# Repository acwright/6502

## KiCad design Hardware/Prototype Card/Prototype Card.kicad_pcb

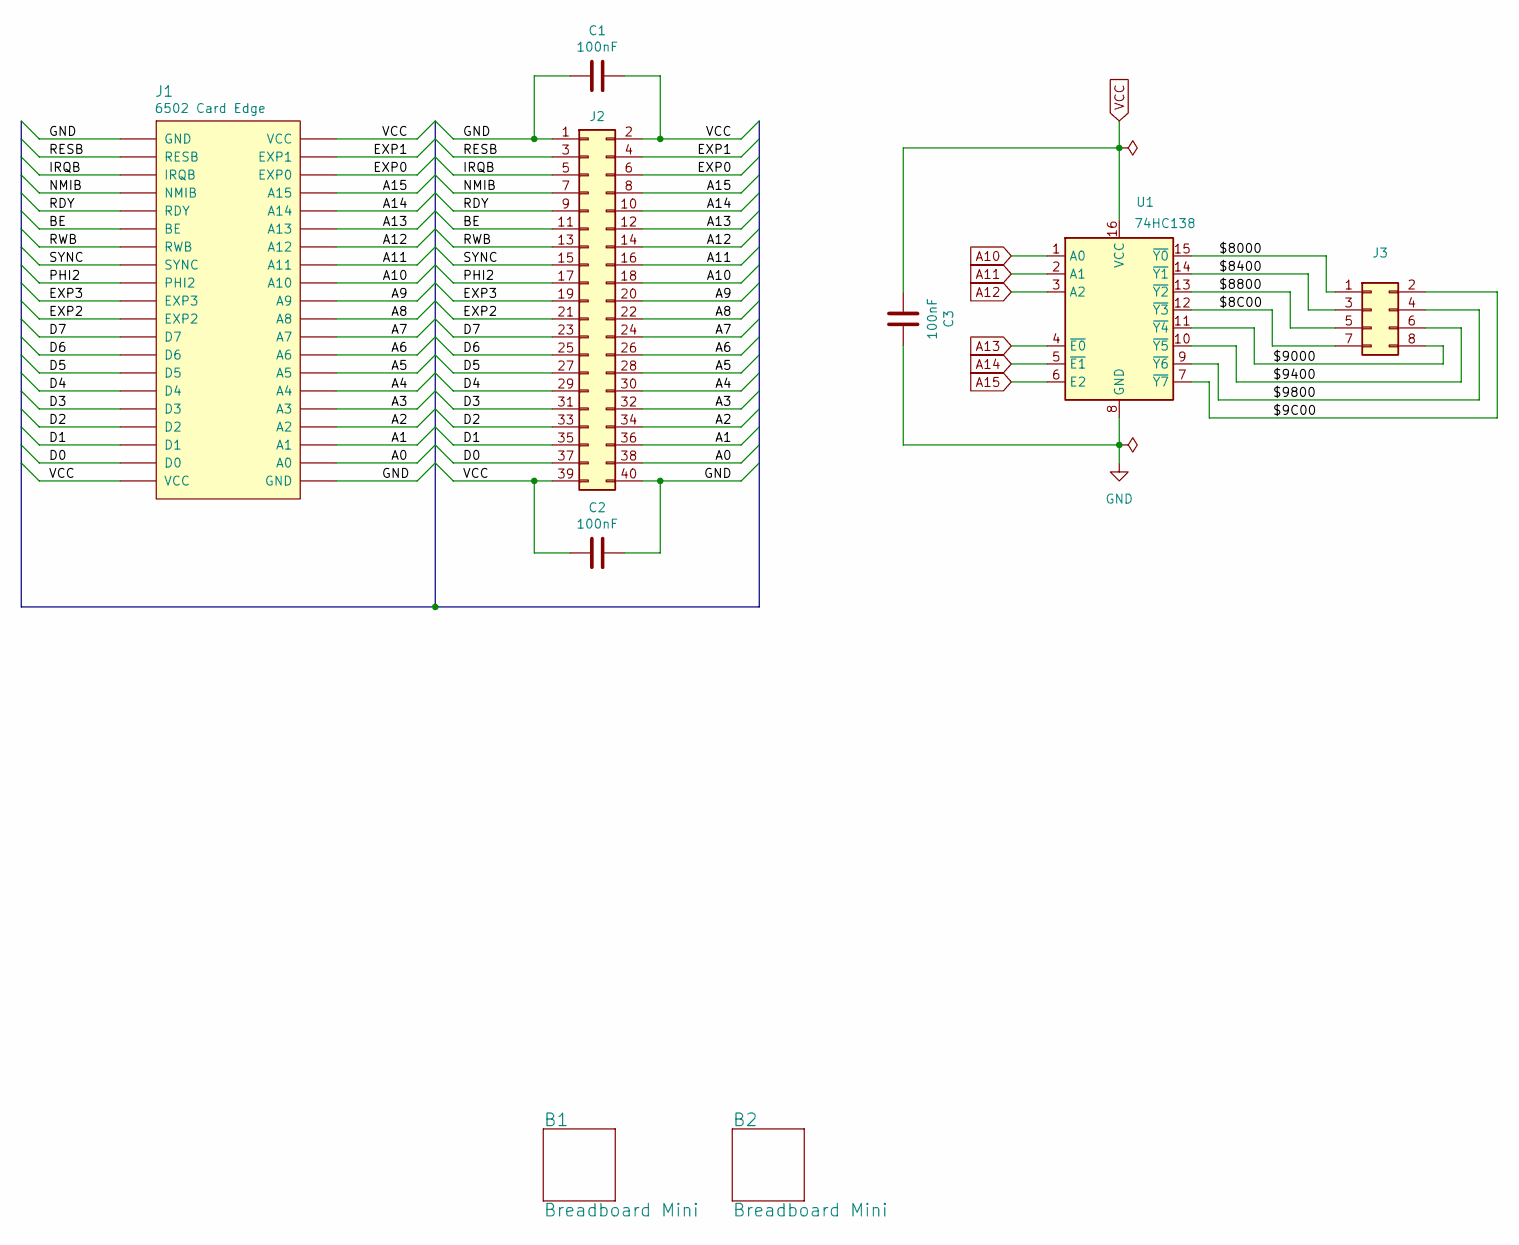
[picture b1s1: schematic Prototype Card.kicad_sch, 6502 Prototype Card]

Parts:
B1, B2: Breadboard Mini
C1, C2, C3: 100nF; C_0805_2012Metric; LCSC C49678
J1: 6502 Card Edge
J2: Conn_02x20_Odd_Even; PinSocket_2x20_P2.54mm_Vertical
J3: Conn_02x04_Odd_Even; PinHeader_2x04_P2.54mm_Vertical
U1: 74HC138; SOIC-16_3.9x9.9mm_P1.27mm; LCSC C5602

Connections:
/$8C00: J3.7, U1.12 (~Y3)
/$9C00: J3.2, U1.7 (~Y7)
/$8000: J3.1, U1.15 (~Y0)
/$8400: J3.3, U1.14 (~Y1)
/$8800: J3.5, U1.13 (~Y2)
/$9000: J3.8, U1.11 (~Y4)
/$9400: J3.6, U1.10 (~Y5)
/$9800: J3.4, U1.9 (~Y6)
/A0: J1.A0, J2.38
/A1: J1.A1, J2.36
/A2: J1.A2, J2.34
/A3: J1.A3, J2.32
/A4: J1.A4, J2.30
/A5: J1.A5, J2.28
/A6: J1.A6, J2.26
/A7: J1.A7, J2.24
/A8: J1.A8, J2.22
/A9: J1.A9, J2.20
/BE: J1.BE, J2.11
/D0: J1.D0, J2.37
/D1: J1.D1, J2.35
/D2: J1.D2, J2.33
/D3: J1.D3, J2.31
/D4: J1.D4, J2.29
/D5: J1.D5, J2.27
/D6: J1.D6, J2.25
/D7: J1.D7, J2.23
/EXP0: J1.EXP0, J2.6
/EXP1: J1.EXP1, J2.4
/EXP2: J1.EXP2, J2.21
/EXP3: J1.EXP3, J2.19
/IRQB: J1.IRQB, J2.5
/NMIB: J1.NMIB, J2.7
/PHI2: J1.PHI2, J2.17
/RDY: J1.RDY, J2.9
/RESB: J1.RESB, J2.3
/RWB: J1.RWB, J2.13
/SYNC: J1.SYNC, J2.15
A10: J1.A10, J2.18, U1.1 (A0)
A11: J1.A11, J2.16, U1.2 (A1)
A12: J1.A12, J2.14, U1.3 (A2)
A13: J1.A13, J2.12, U1.4 (~E0)
A14: J1.A14, J2.10, U1.5 (~E1)
A15: J1.A15, J2.8, U1.6 (E2)
GND: C1.1, C2.2, C3.2, J1.GND, J2.1, J2.40, U1.8 (GND)
VCC: C1.2, C2.1, C3.1, J1.VCC, J2.2, J2.39, U1.16 (VCC)

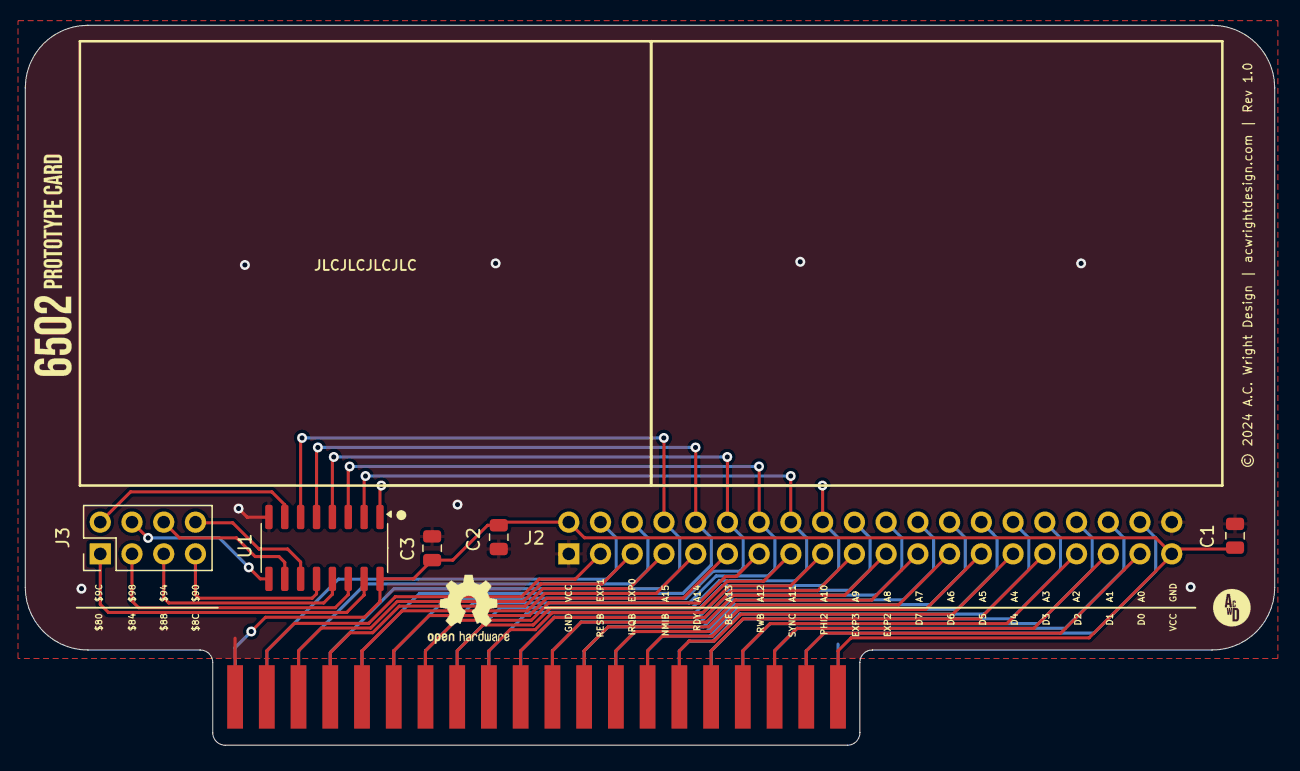
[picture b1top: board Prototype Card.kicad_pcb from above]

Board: 2 copper layers, 100.0 x 57.6 mm, 9 parts (1 on the bottom side), 46 nets.

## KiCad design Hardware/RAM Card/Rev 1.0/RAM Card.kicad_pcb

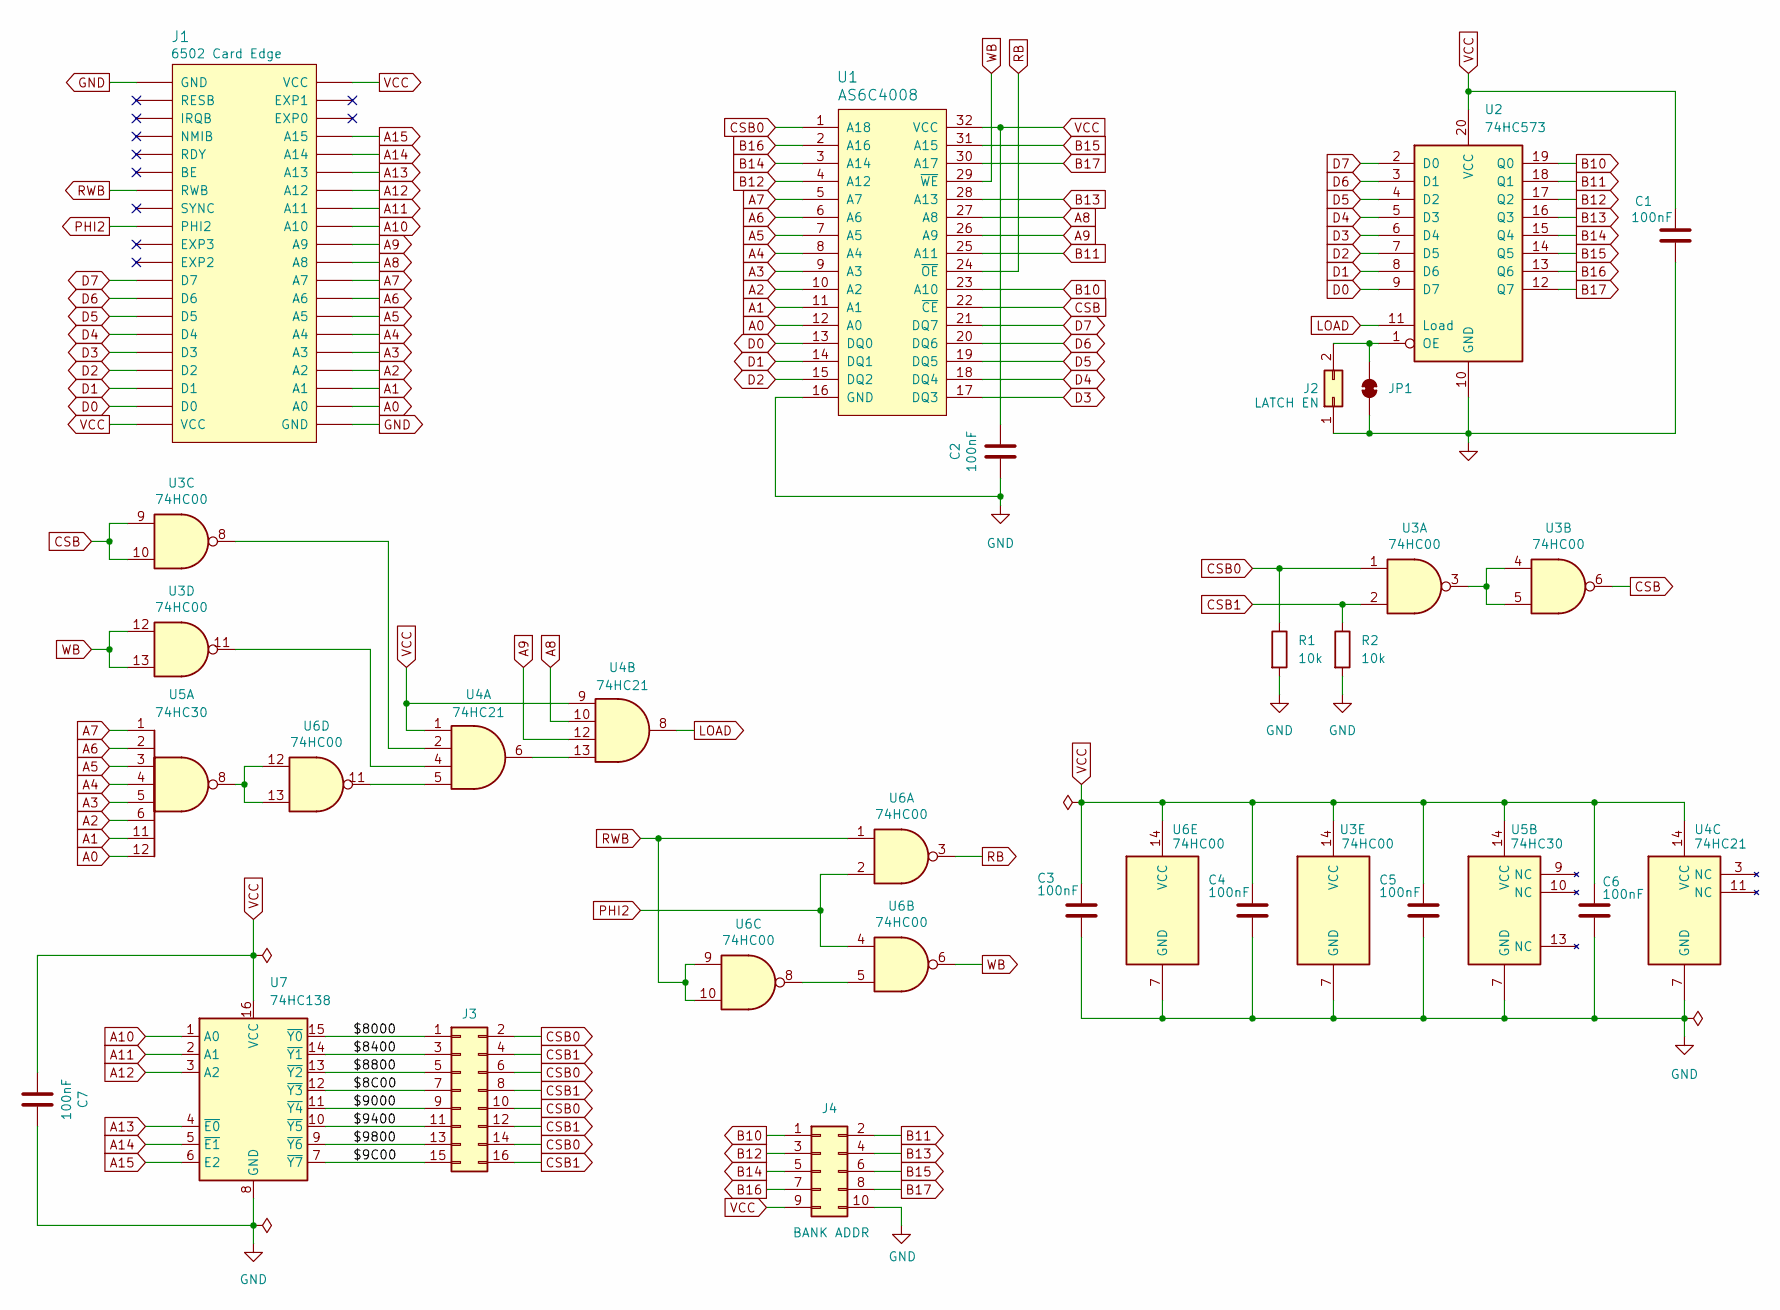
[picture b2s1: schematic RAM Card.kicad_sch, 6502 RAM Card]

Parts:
C1, C2, C3, C4, C5, C6, C7: 100nF; C_0805_2012Metric; LCSC C49678
J1: 6502 Card Edge
J2: LATCH EN; PinHeader_1x02_P2.54mm_Vertical
J3: Conn_02x08_Odd_Even; PinHeader_2x08_P2.54mm_Vertical
J4: BANK ADDR; PinHeader_2x05_P2.54mm_Vertical
JP1: Latch Enable; SolderJumper-2_P1.3mm_Bridged_RoundedPad1.0x1.5mm
R1, R2: 10k; R_0805_2012Metric; LCSC C17414
U1: AS6C4008; DIP-32_W15.24mm_Socket_LongPads
U2: 74HC573; SOIC-20W_7.5x12.8mm_P1.27mm; LCSC C5608
U3, U6: 74HC00; SOIC-14_3.9x8.7mm_P1.27mm; LCSC C5586
U4: 74HC21; SOIC-14_3.9x8.7mm_P1.27mm; LCSC C75398
U5: 74HC30; SOIC-14_3.9x8.7mm_P1.27mm; LCSC C19818870
U7: 74HC138; SOIC-16_3.9x9.9mm_P1.27mm; LCSC C5602

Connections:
/$8C00: J3.7, U7.12 (~Y3)
/$9C00: J3.15, U7.7 (~Y7)
/$8000: J3.1, U7.15 (~Y0)
/$8400: J3.3, U7.14 (~Y1)
/$8800: J3.5, U7.13 (~Y2)
/$9000: J3.9, U7.11 (~Y4)
/$9400: J3.11, U7.10 (~Y5)
/$9800: J3.13, U7.9 (~Y6)
A0: J1.A0, U1.12 (A0), U5.12
A1: J1.A1, U1.11 (A1), U5.11
A2: J1.A2, U1.10 (A2), U5.6
A3: J1.A3, U1.9 (A3), U5.5
A4: J1.A4, U1.8 (A4), U5.4
A5: J1.A5, U1.7 (A5), U5.3
A6: J1.A6, U1.6 (A6), U5.2
A7: J1.A7, U1.5 (A7), U5.1
A8: J1.A8, U1.27 (A8), U4.10
A9: J1.A9, U1.26 (A9), U4.12
A10: J1.A10, U7.1 (A0)
A11: J1.A11, U7.2 (A1)
A12: J1.A12, U7.3 (A2)
A13: J1.A13, U7.4 (~E0)
A14: J1.A14, U7.5 (~E1)
A15: J1.A15, U7.6 (E2)
B10: J4.1, U1.23 (A10), U2.19 (Q0)
B11: J4.2, U1.25 (A11), U2.18 (Q1)
B12: J4.3, U1.4 (A12), U2.17 (Q2)
B13: J4.4, U1.28 (A13), U2.16 (Q3)
B14: J4.5, U1.3 (A14), U2.15 (Q4)
B15: J4.6, U1.31 (A15), U2.14 (Q5)
B16: J4.7, U1.2 (A16), U2.13 (Q6)
B17: J4.8, U1.30 (A17), U2.12 (Q7)
CSB: U1.22 (~CE), U3.6, U3.9, U3.10
CSB0: J3.2, J3.6, J3.10, J3.14, R1.1, U1.1 (A18), U3.1
CSB1: J3.4, J3.8, J3.12, J3.16, R2.1, U3.2
D0: J1.D0, U1.13 (DQ0), U2.9 (D7)
D1: J1.D1, U1.14 (DQ1), U2.8 (D6)
D2: J1.D2, U1.15 (DQ2), U2.7 (D5)
D3: J1.D3, U1.17 (DQ3), U2.6 (D4)
D4: J1.D4, U1.18 (DQ4), U2.5 (D3)
D5: J1.D5, U1.19 (DQ5), U2.4 (D2)
D6: J1.D6, U1.20 (DQ6), U2.3 (D1)
D7: J1.D7, U1.21 (DQ7), U2.2 (D0)
GND: C1.2, C2.2, C3.2, C4.2, C5.2, C6.2, C7.2, J1.GND, J2.1, J4.10, JP1.1 (A), R1.2, R2.2, U1.16 (GND), U2.10 (GND), U3.7 (GND), U4.7 (GND), U5.7 (GND), U6.7 (GND), U7.8 (GND)
LOAD: U2.11 (Load), U4.8
unnamed: J2.2, JP1.2 (B), U2.1 (OE)
unnamed: U3.3, U3.4, U3.5
unnamed: U3.8, U4.2
unnamed: U3.11, U4.4
unnamed: U4.5, U6.11
unnamed: U4.6, U4.13
unnamed: U5.8, U6.12, U6.13
unnamed: U6.5, U6.8
PHI2: J1.PHI2, U6.2, U6.4
RB: U1.24 (~OE), U6.3
RWB: J1.RWB, U6.1, U6.9, U6.10
VCC: C1.1, C2.1, C3.1, C4.1, C5.1, C6.1, C7.1, J1.VCC, J4.9, U1.32 (VCC), U2.20 (VCC), U3.14 (VCC), U4.1, U4.9, U4.14 (VCC), U5.14 (VCC), U6.14 (VCC), U7.16 (VCC)
WB: U1.29 (~WE), U3.12, U3.13, U6.6

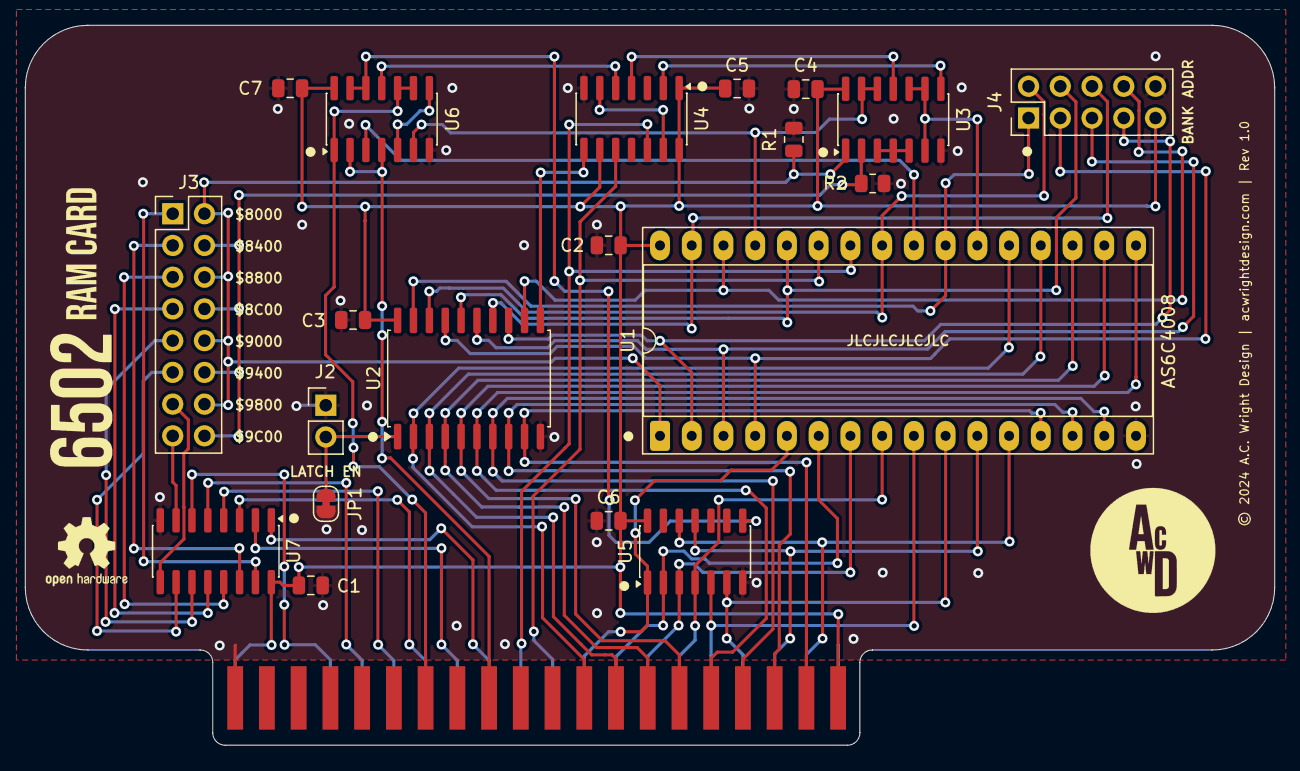
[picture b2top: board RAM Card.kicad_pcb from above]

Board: 2 copper layers, 100.0 x 57.6 mm, 21 parts (0 on the bottom side), 58 nets.

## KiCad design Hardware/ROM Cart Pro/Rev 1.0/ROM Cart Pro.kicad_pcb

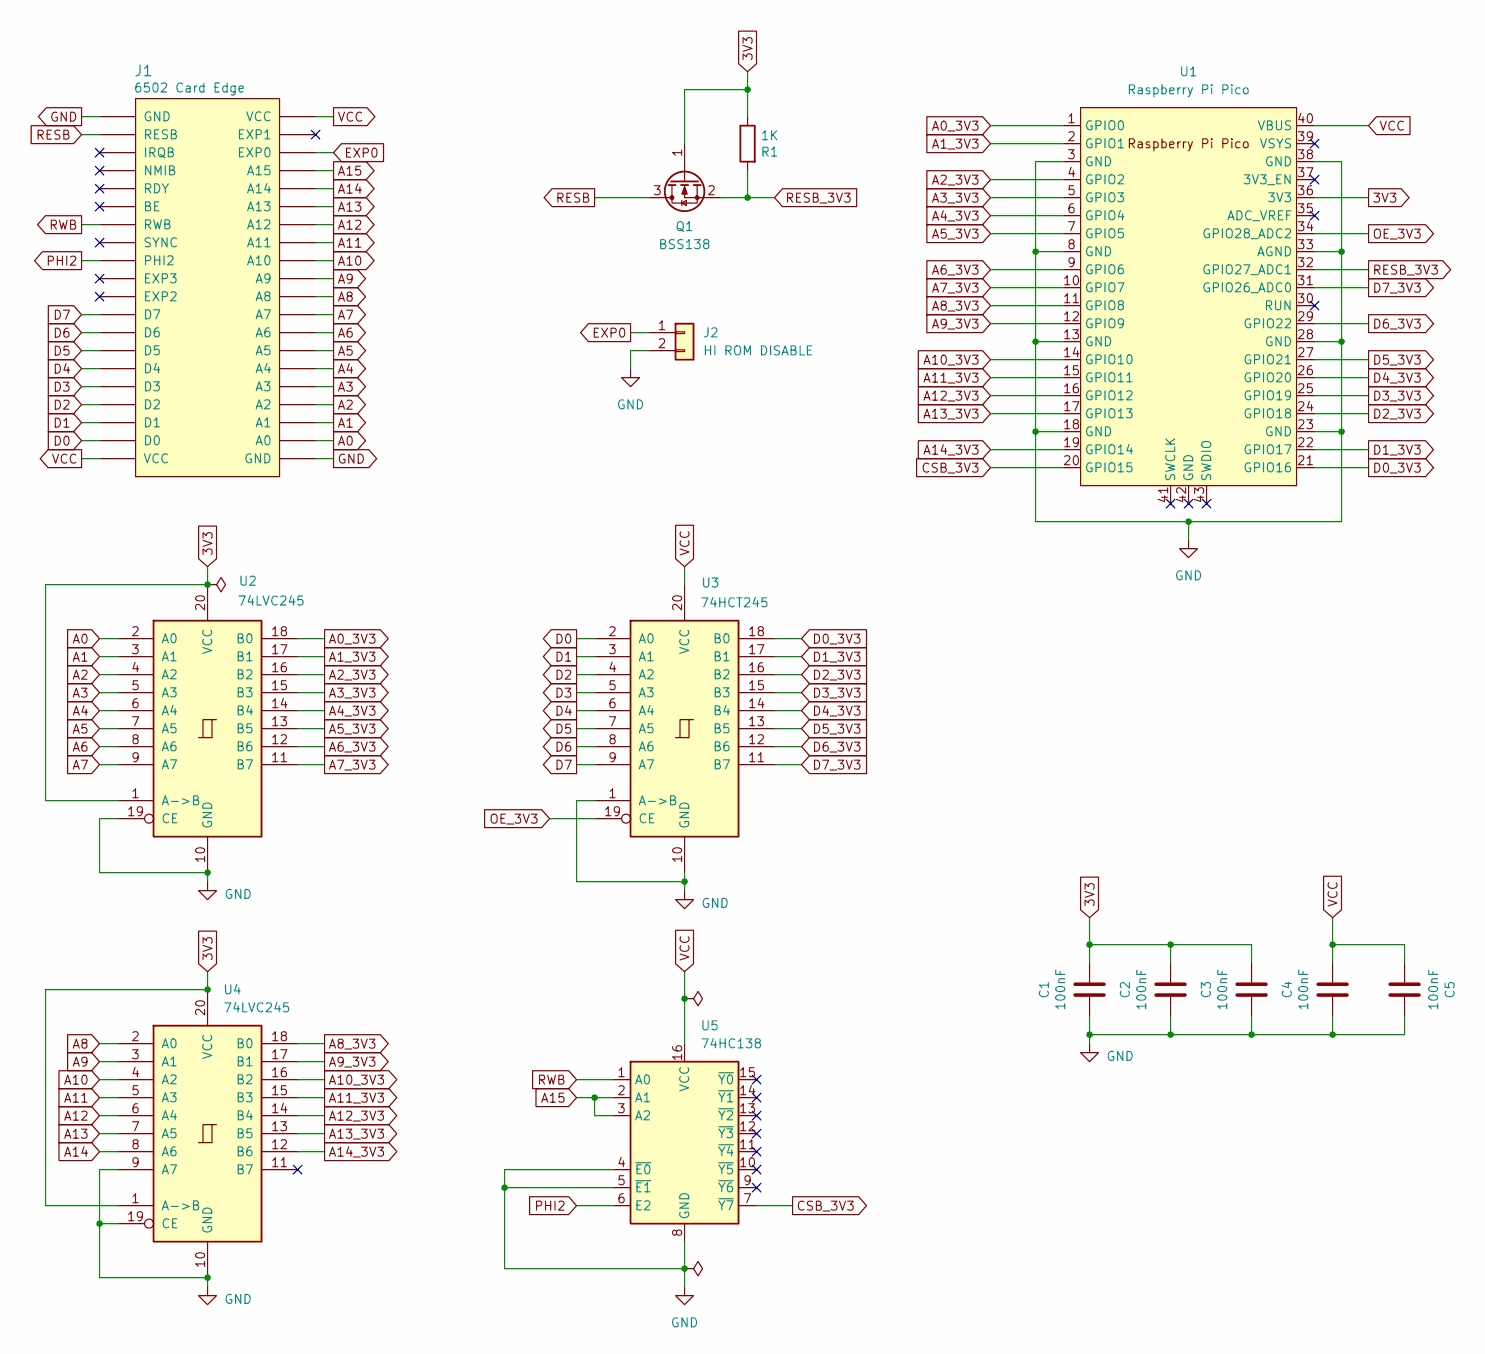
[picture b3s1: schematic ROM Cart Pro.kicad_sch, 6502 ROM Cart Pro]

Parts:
C1, C2, C3, C4, C5: 100nF; C_0805_2012Metric; LCSC C49678
J1: 6502 Card Edge
J2: HI ROM DISABLE; PinHeader_1x02_P2.54mm_Vertical
Q1: BSS138; SOT-23; LCSC C78284
R1: 1K; R_0805_2012Metric; LCSC C17513
U1: Raspberry Pi Pico
U2, U4: 74LVC245; TSSOP-20_4.4x6.5mm_P0.65mm; LCSC C6082
U3: 74HCT245; TSSOP-20_4.4x6.5mm_P0.65mm; LCSC C5980
U5: 74HC138; SOIC-16_3.9x9.9mm_P1.27mm; LCSC C5602

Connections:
3V3: C1.1, C2.1, C3.1, Q1.1 (G), R1.1, U1.36 (3V3), U2.1 (A->B), U2.20 (VCC), U4.1 (A->B), U4.20 (VCC)
A0: J1.A0, U2.2 (A0)
A0_3V3: U1.1 (GPIO0), U2.18 (B0)
A1: J1.A1, U2.3 (A1)
A1_3V3: U1.2 (GPIO1), U2.17 (B1)
A2: J1.A2, U2.4 (A2)
A2_3V3: U1.4 (GPIO2), U2.16 (B2)
A3: J1.A3, U2.5 (A3)
A3_3V3: U1.5 (GPIO3), U2.15 (B3)
A4: J1.A4, U2.6 (A4)
A4_3V3: U1.6 (GPIO4), U2.14 (B4)
A5: J1.A5, U2.7 (A5)
A5_3V3: U1.7 (GPIO5), U2.13 (B5)
A6: J1.A6, U2.8 (A6)
A6_3V3: U1.9 (GPIO6), U2.12 (B6)
A7: J1.A7, U2.9 (A7)
A7_3V3: U1.10 (GPIO7), U2.11 (B7)
A8: J1.A8, U4.2 (A0)
A8_3V3: U1.11 (GPIO8), U4.18 (B0)
A9: J1.A9, U4.3 (A1)
A9_3V3: U1.12 (GPIO9), U4.17 (B1)
A10: J1.A10, U4.4 (A2)
A10_3V3: U1.14 (GPIO10), U4.16 (B2)
A11: J1.A11, U4.5 (A3)
A11_3V3: U1.15 (GPIO11), U4.15 (B3)
A12: J1.A12, U4.6 (A4)
A12_3V3: U1.16 (GPIO12), U4.14 (B4)
A13: J1.A13, U4.7 (A5)
A13_3V3: U1.17 (GPIO13), U4.13 (B5)
A14: J1.A14, U4.8 (A6)
A14_3V3: U1.19 (GPIO14), U4.12 (B6)
A15: J1.A15, U5.2 (A1), U5.3 (A2)
CSB_3V3: U1.20 (GPIO15), U5.7 (~Y7)
D0: J1.D0, U3.2 (A0)
D0_3V3: U1.21 (GPIO16), U3.18 (B0)
D1: J1.D1, U3.3 (A1)
D1_3V3: U1.22 (GPIO17), U3.17 (B1)
D2: J1.D2, U3.4 (A2)
D2_3V3: U1.24 (GPIO18), U3.16 (B2)
D3: J1.D3, U3.5 (A3)
D3_3V3: U1.25 (GPIO19), U3.15 (B3)
D4: J1.D4, U3.6 (A4)
D4_3V3: U1.26 (GPIO20), U3.14 (B4)
D5: J1.D5, U3.7 (A5)
D5_3V3: U1.27 (GPIO21), U3.13 (B5)
D6: J1.D6, U3.8 (A6)
D6_3V3: U1.29 (GPIO22), U3.12 (B6)
D7: J1.D7, U3.9 (A7)
D7_3V3: U1.31 (GPIO26_ADC0), U3.11 (B7)
EXP0: J1.EXP0, J2.1
GND: C1.2, C2.2, C3.2, C4.2, C5.2, J1.GND, J2.2, U1.3 (GND), U1.8 (GND), U1.13 (GND), U1.18 (GND), U1.23 (GND), U1.28 (GND), U1.33 (AGND), U1.38 (GND), U2.10 (GND), U2.19 (CE), U3.1 (A->B), U3.10 (GND), U4.9 (A7), U4.10 (GND), U4.19 (CE), U5.4 (~E0), U5.5 (~E1), U5.8 (GND)
OE_3V3: U1.34 (GPIO28_ADC2), U3.19 (CE)
PHI2: J1.PHI2, U5.6 (E2)
RESB: J1.RESB, Q1.3 (D)
RESB_3V3: Q1.2 (S), R1.2, U1.32 (GPIO27_ADC1)
RWB: J1.RWB, U5.1 (A0)
VCC: C4.1, C5.1, J1.VCC, U1.40 (VBUS), U3.20 (VCC), U5.16 (VCC)

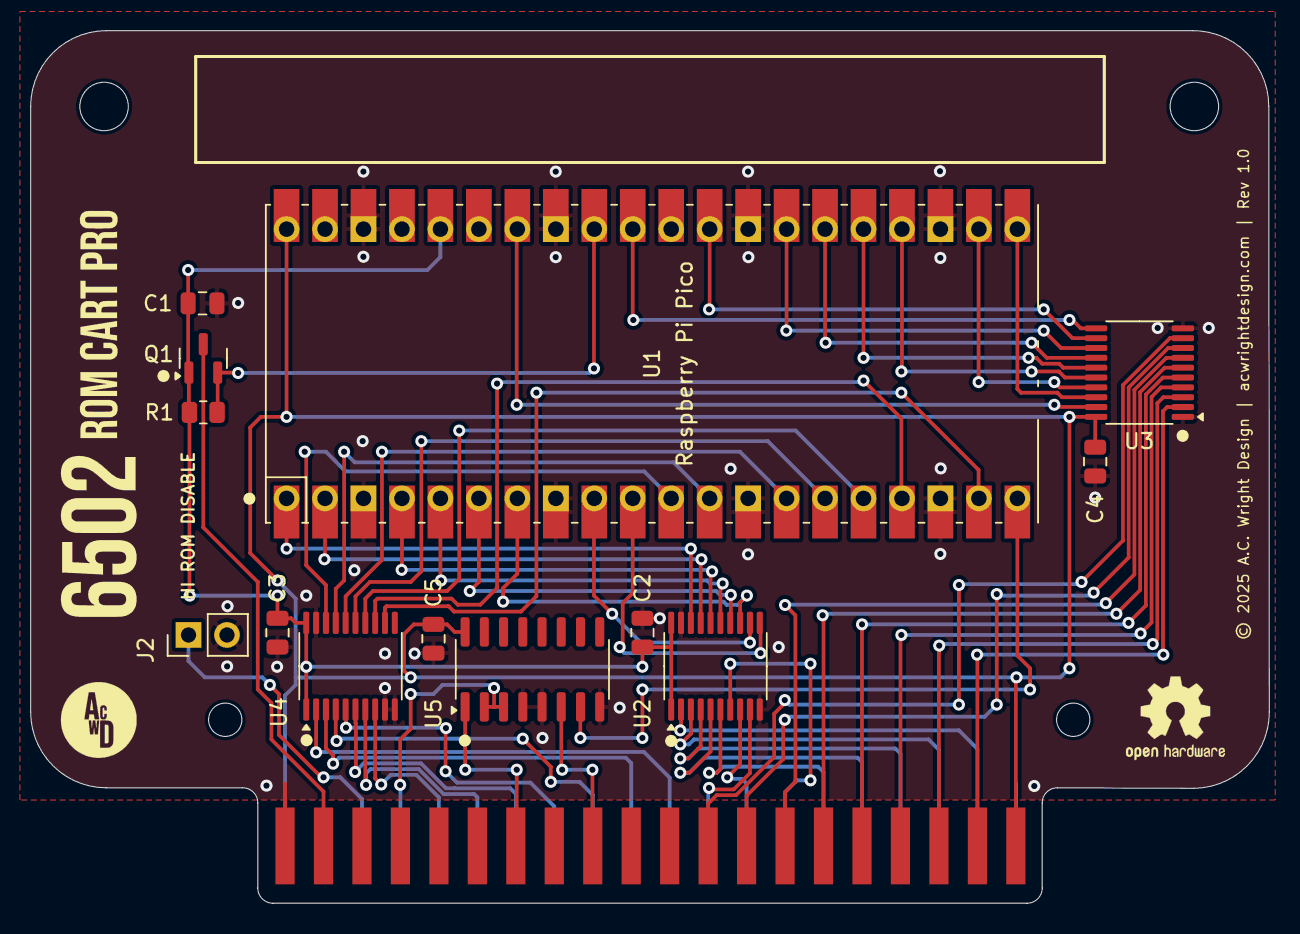
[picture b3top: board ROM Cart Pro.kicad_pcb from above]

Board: 2 copper layers, 81.8 x 57.6 mm, 14 parts (0 on the bottom side), 57 nets.

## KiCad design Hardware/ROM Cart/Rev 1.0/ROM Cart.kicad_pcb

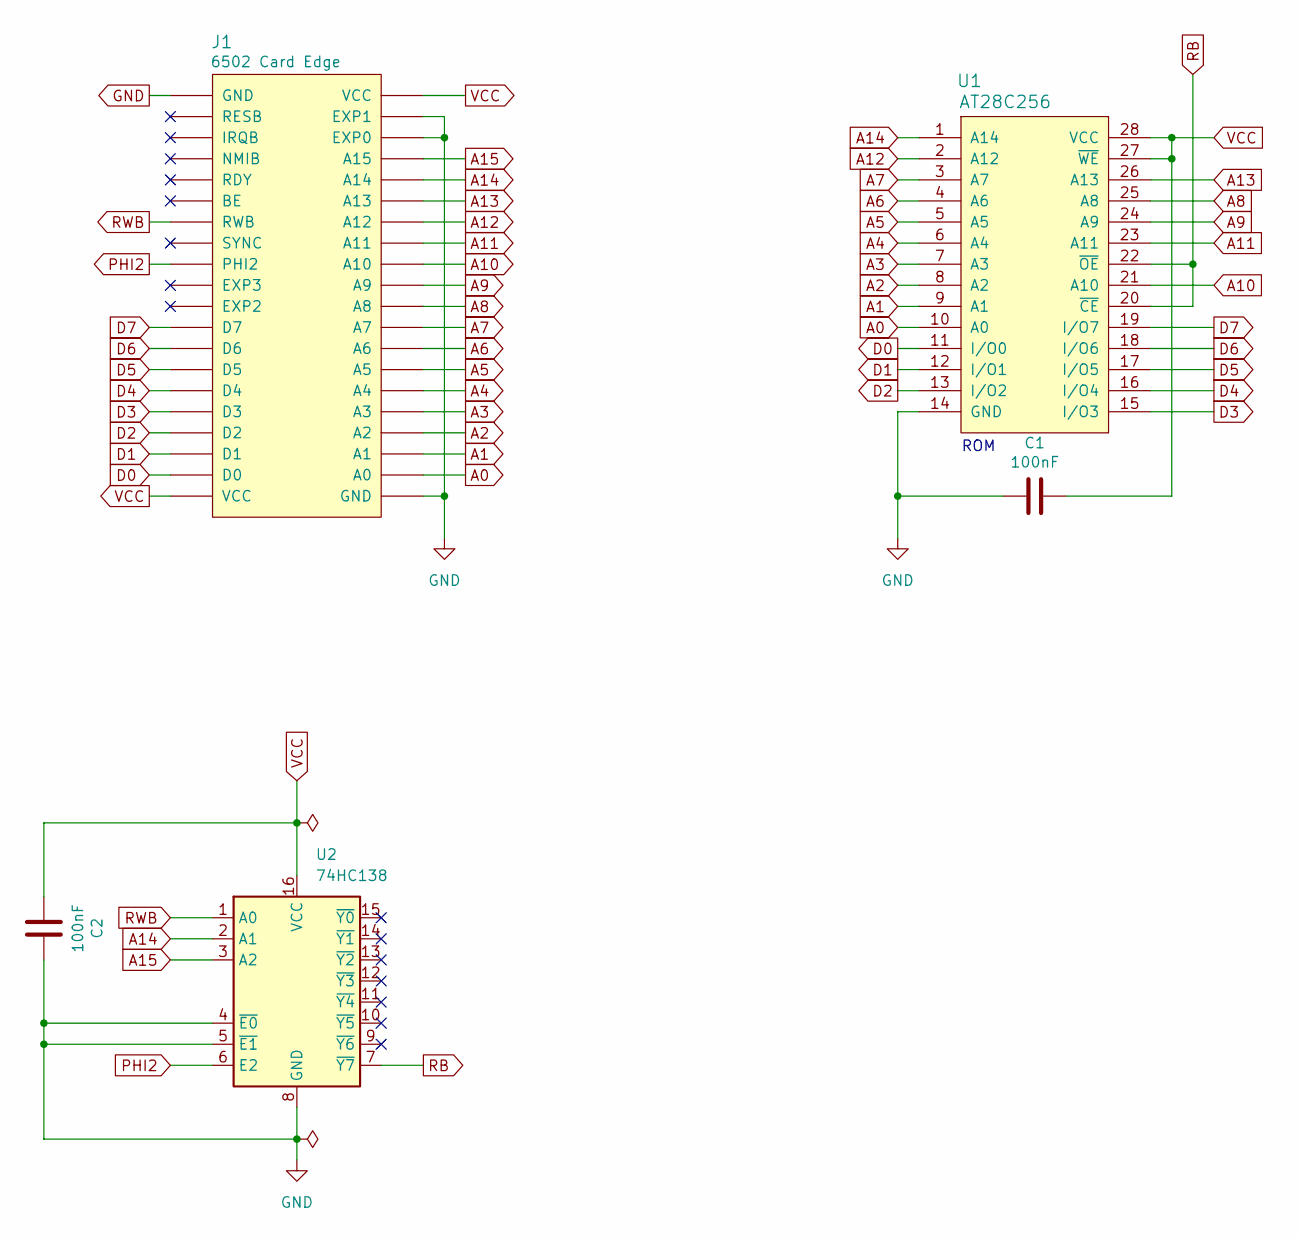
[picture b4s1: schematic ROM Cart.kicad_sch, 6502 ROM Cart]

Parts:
C1, C2: 100nF; C_Disc_D5.0mm_W2.5mm_P5.00mm
J1: 6502 Card Edge
U1: AT28C256; DIP-28_W15.24mm_Socket_LongPads
U2: 74HC138; DIP-16_W7.62mm_Socket_LongPads

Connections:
A0: J1.A0, U1.10 (A0)
A1: J1.A1, U1.9 (A1)
A2: J1.A2, U1.8 (A2)
A3: J1.A3, U1.7 (A3)
A4: J1.A4, U1.6 (A4)
A5: J1.A5, U1.5 (A5)
A6: J1.A6, U1.4 (A6)
A7: J1.A7, U1.3 (A7)
A8: J1.A8, U1.25 (A8)
A9: J1.A9, U1.24 (A9)
A10: J1.A10, U1.21 (A10)
A11: J1.A11, U1.23 (A11)
A12: J1.A12, U1.2 (A12)
A13: J1.A13, U1.26 (A13)
A14: J1.A14, U1.1 (A14), U2.2 (A1)
A15: J1.A15, U2.3 (A2)
D0: J1.D0, U1.11 (I/O0)
D1: J1.D1, U1.12 (I/O1)
D2: J1.D2, U1.13 (I/O2)
D3: J1.D3, U1.15 (I/O3)
D4: J1.D4, U1.16 (I/O4)
D5: J1.D5, U1.17 (I/O5)
D6: J1.D6, U1.18 (I/O6)
D7: J1.D7, U1.19 (I/O7)
GND: C1.2, C2.2, J1.EXP0, J1.EXP1, J1.GND, U1.14 (GND), U2.4 (~E0), U2.5 (~E1), U2.8 (GND)
PHI2: J1.PHI2, U2.6 (E2)
RB: U1.20 (~CE), U1.22 (~OE), U2.7 (~Y7)
RWB: J1.RWB, U2.1 (A0)
VCC: C1.1, C2.1, J1.VCC, U1.27 (~WE), U1.28 (VCC), U2.16 (VCC)

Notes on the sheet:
ROM

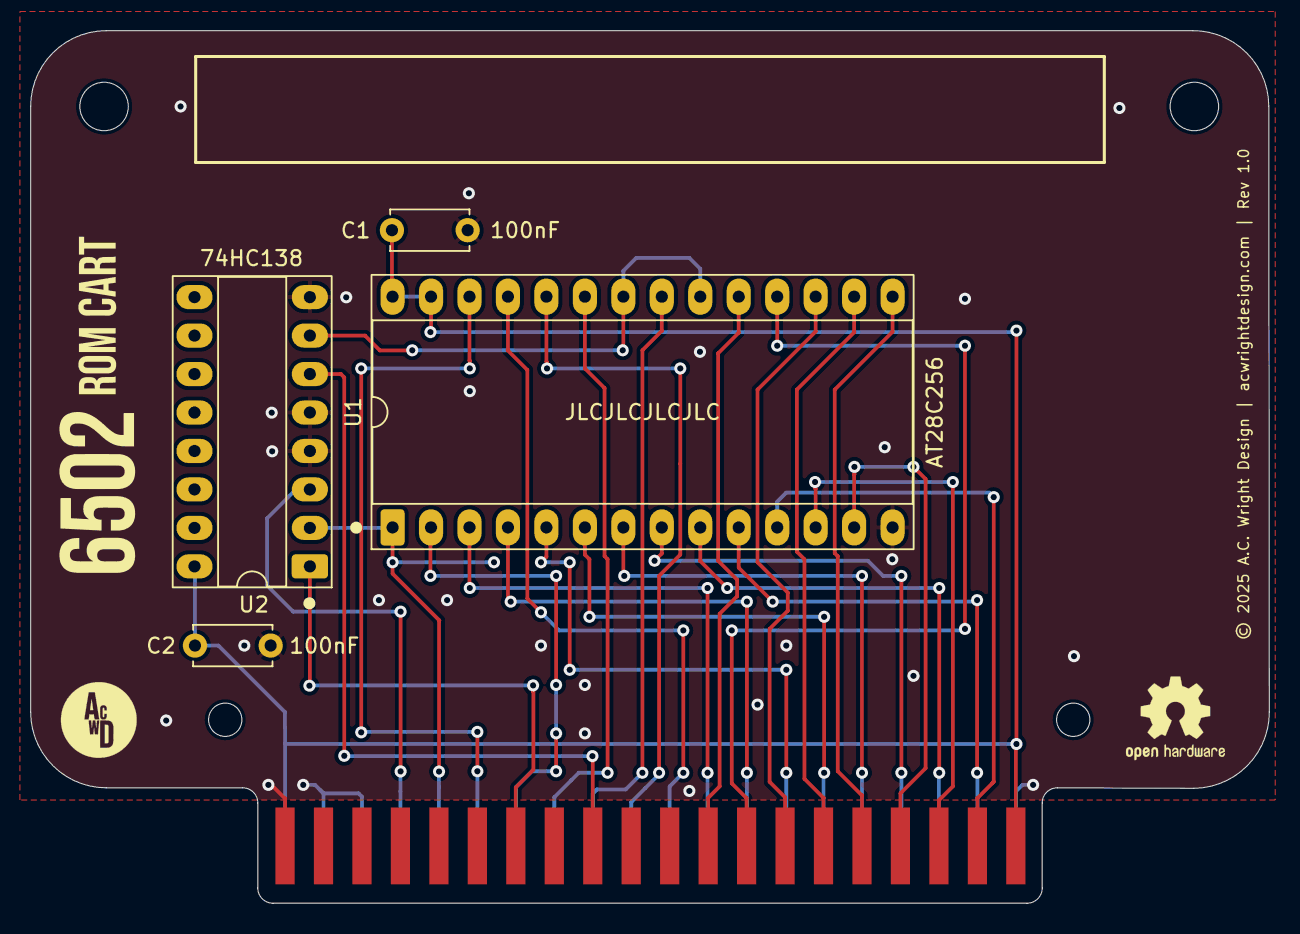
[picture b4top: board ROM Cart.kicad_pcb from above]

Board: 2 copper layers, 81.8 x 57.6 mm, 9 parts (0 on the bottom side), 29 nets.

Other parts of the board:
H1, H2: MountingHole; MountingHole_3.2mm_M3
H3, H4: MountingHole; MountingHole_2.2mm_M2

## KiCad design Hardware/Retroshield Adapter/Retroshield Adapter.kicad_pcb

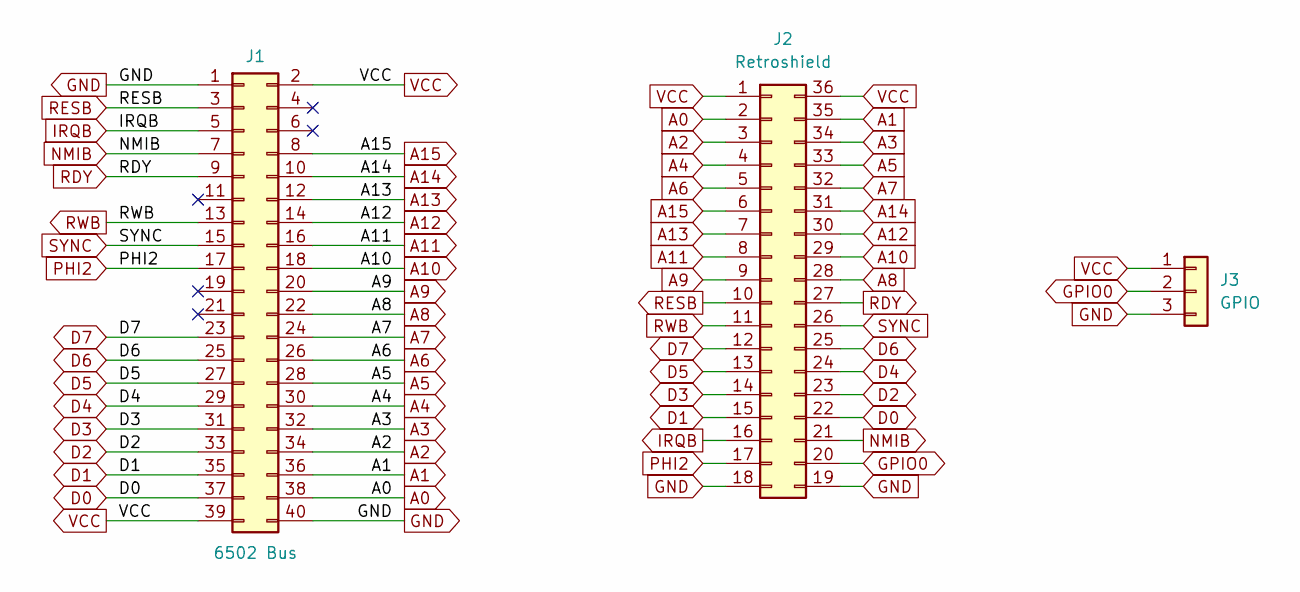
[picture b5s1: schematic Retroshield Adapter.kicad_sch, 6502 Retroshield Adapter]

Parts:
J1: 6502 Bus; PinHeader_2x20_P2.54mm_Vertical
J2: Retroshield; Retroshield Header
J3: GPIO; PinHeader_1x03_P2.54mm_Vertical

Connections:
A0: J1.38, J2.2
A1: J1.36, J2.35
A2: J1.34, J2.3
A3: J1.32, J2.34
A4: J1.30, J2.4
A5: J1.28, J2.33
A6: J1.26, J2.5
A7: J1.24, J2.32
A8: J1.22, J2.28
A9: J1.20, J2.9
A10: J1.18, J2.29
A11: J1.16, J2.8
A12: J1.14, J2.30
A13: J1.12, J2.7
A14: J1.10, J2.31
A15: J1.8, J2.6
D0: J1.37, J2.22
D1: J1.35, J2.15
D2: J1.33, J2.23
D3: J1.31, J2.14
D4: J1.29, J2.24
D5: J1.27, J2.13
D6: J1.25, J2.25
D7: J1.23, J2.12
GND: J1.1, J1.40, J2.18, J2.19, J3.3
GPIO0: J2.20, J3.2
IRQB: J1.5, J2.16
NMIB: J1.7, J2.21
PHI2: J1.17, J2.17
RDY: J1.9, J2.27
RESB: J1.3, J2.10
RWB: J1.13, J2.11
SYNC: J1.15, J2.26
VCC: J1.2, J1.39, J2.1, J2.36, J3.1

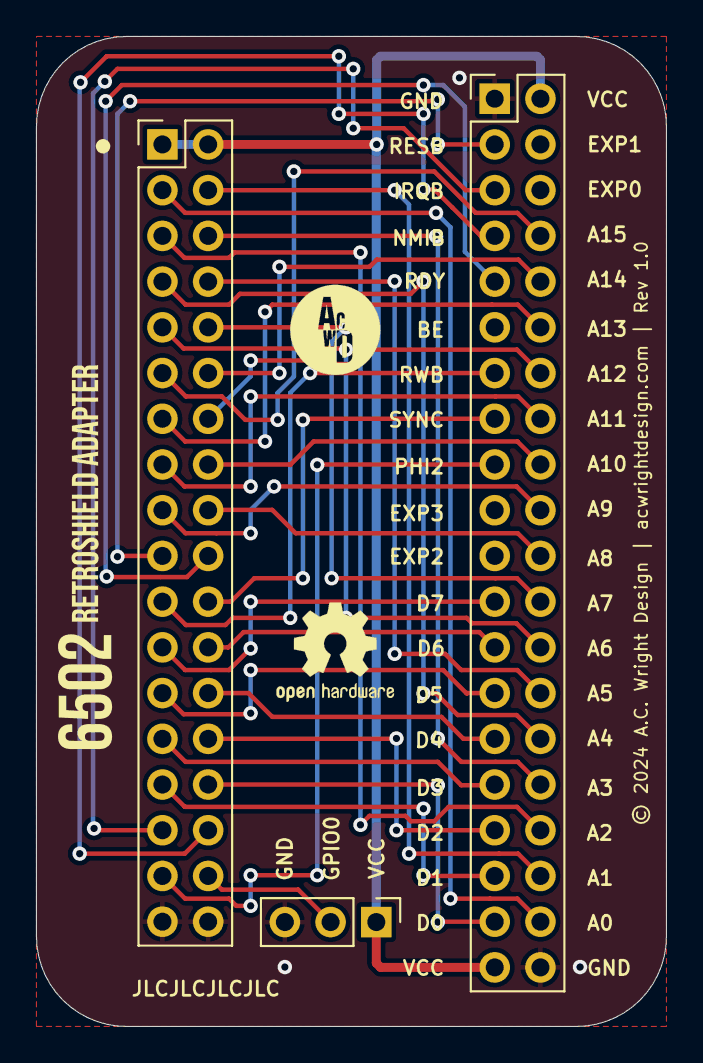
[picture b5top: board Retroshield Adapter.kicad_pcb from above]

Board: 2 copper layers, 35.0 x 55.0 mm, 3 parts (0 on the bottom side), 34 nets.

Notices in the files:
Hardware/Prototype Card/Prototype Card.kicad_pcb:
© 2024 A.C. Wright Design | acwrightdesign.com | Rev 1.0
Hardware/ROM Cart Pro/Rev 1.0/ROM Cart Pro.kicad_pcb:
© 2025 A.C. Wright Design | acwrightdesign.com | Rev 1.0
